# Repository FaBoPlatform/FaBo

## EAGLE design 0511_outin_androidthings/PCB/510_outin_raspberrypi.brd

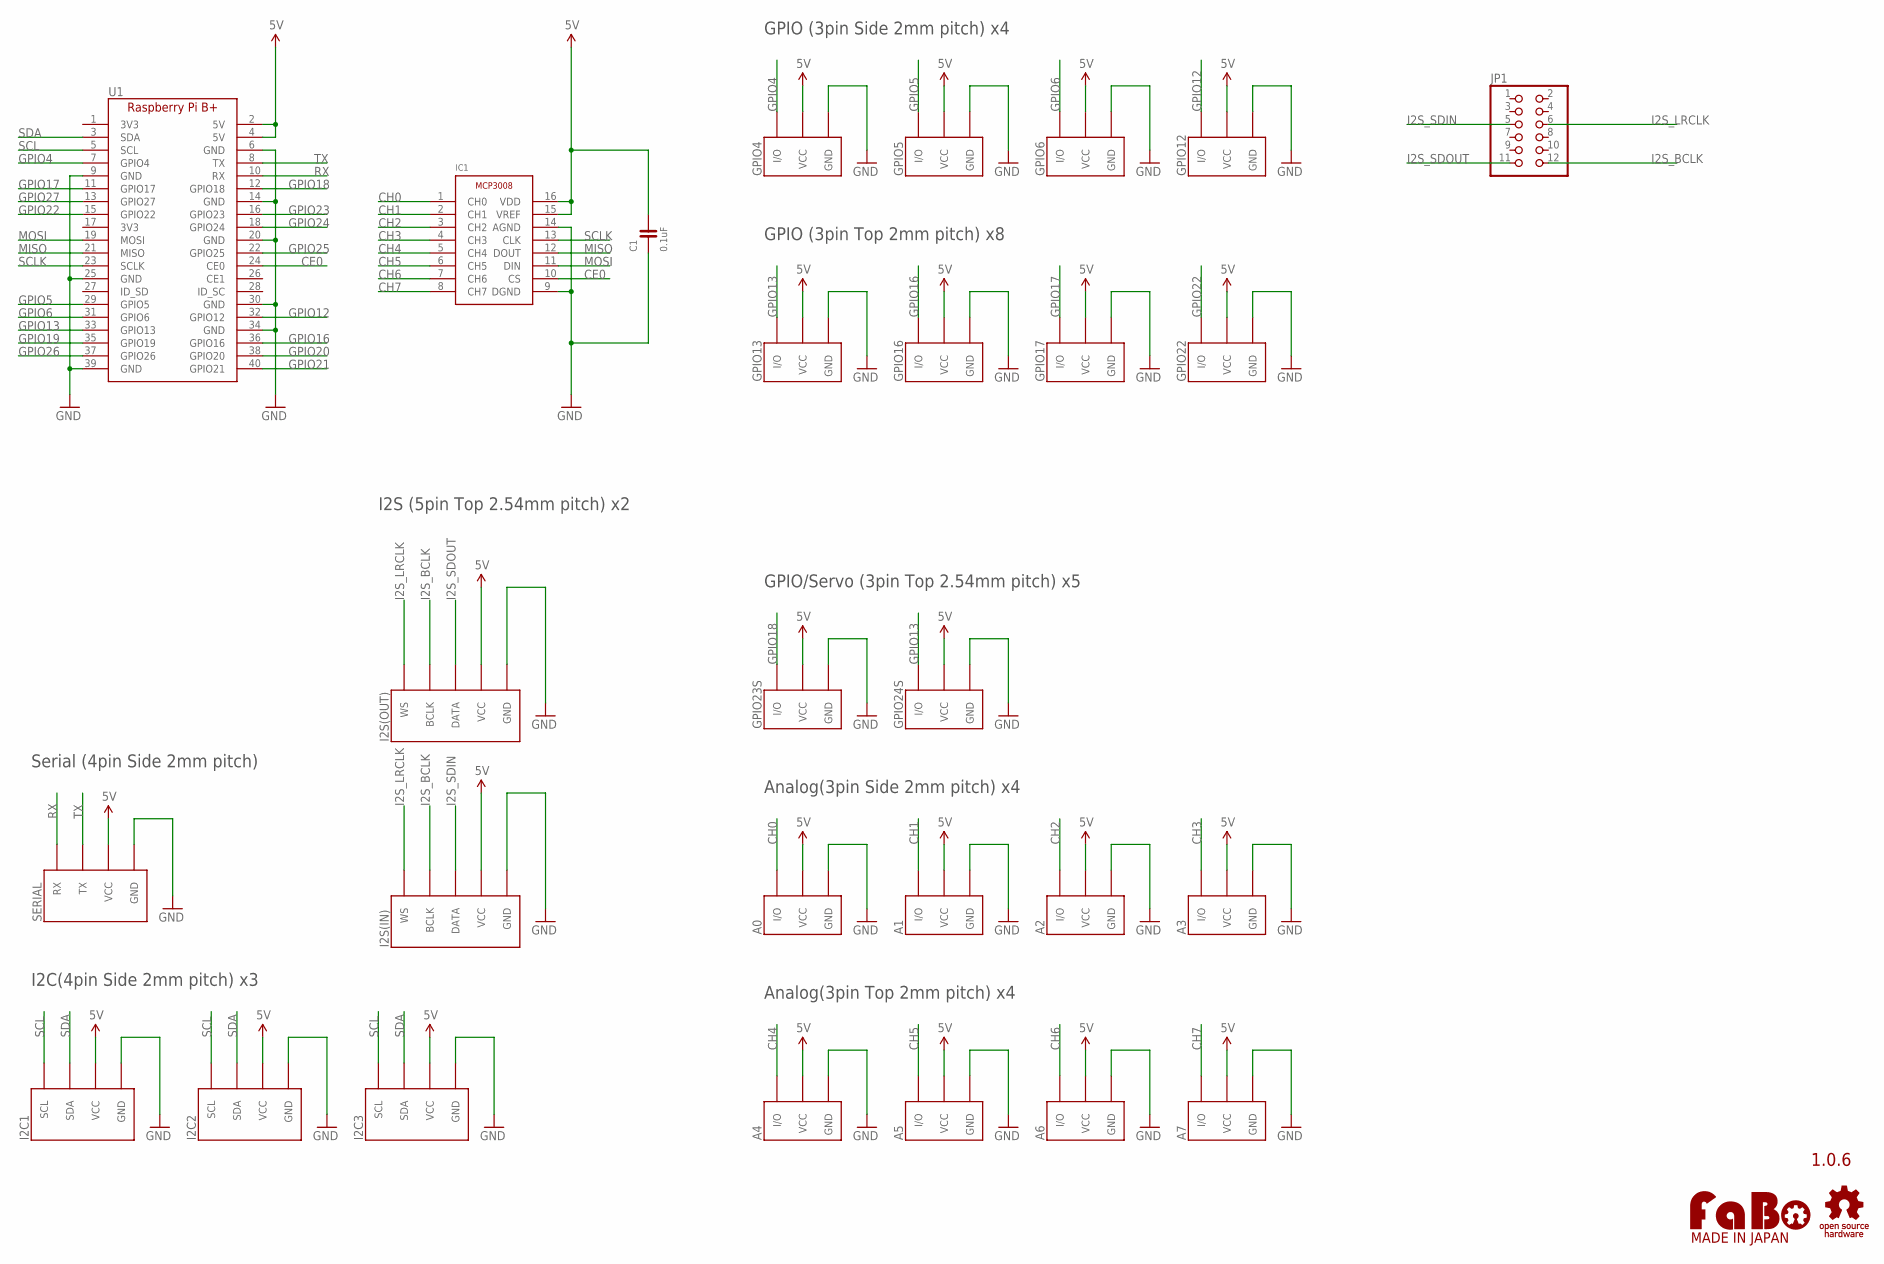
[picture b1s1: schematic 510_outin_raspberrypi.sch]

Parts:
A0, A1, A2, A3: FABO_BRICK_3PIN-S03B-PASK-2; FABO_BRICK_3PIN_S03B-PASK-2
A4, A5, A6, A7: FABO_BRICK_3PIN-B03B-PASK-1; FABO_BRICK_3PIN_B03B-PASK-1
C1: 0.1uF; 0603
GPIO4, GPIO5, GPIO6, GPIO12: FABO_BRICK_3PIN-S03B-PASK-2; FABO_BRICK_3PIN_S03B-PASK-2
GPIO13, GPIO16, GPIO17, GPIO22: FABO_BRICK_3PIN-B03B-PASK-1; FABO_BRICK_3PIN_B03B-PASK-1
GPIO23S, GPIO24S: FABO_BRICK_3PIN-HEADER; FABO_BRICK_3PIN_HEADER
I2C1, I2C2, I2C3: FABO_BRICK_I2C-S04B-PASK-2; FABO_BRICK_I2C_S04B-PASK-2
I2S(IN), I2S(OUT): FABO_BRICK_I2SLONG; FABO_BRICK_I2S_S05B-PASK-2_LONG
IC1: MICROCHIP-MCP3008
JP1: PINHD-2X6; 2X06
SERIAL: FABO_BRICK_SERIAL-S04B-PASK-2; FABO_BRICK_SERIAL_S04B-PASK-2
U1: RASPBERRY_PI_B+
U$4: LOGO_OSHW-T_M_BOTTOM; LOGO_OSHW_T_MS_BOTTOM
U$14: LOGO_FABO-M; LOGO_FABO_MS

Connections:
5V: A0.VCC, A1.VCC, A2.VCC, A3.VCC, A4.VCC, A5.VCC, A6.VCC, A7.VCC, C1.2, GPIO4.VCC, GPIO5.VCC, GPIO6.VCC, GPIO12.VCC, GPIO13.VCC, GPIO16.VCC, GPIO17.VCC, GPIO22.VCC, GPIO23S.VCC, GPIO24S.VCC, I2C1.VCC, I2C2.VCC, I2C3.VCC, I2S(IN).VCC, I2S(OUT).VCC, IC1.15 (VREF), IC1.16 (VDD), SERIAL.VCC, U1.2 (5V), U1.4 (5V)
CE0: IC1.10 (CS), U1.24 (CE0)
CH0: A0.I/O, IC1.1 (CH0)
CH1: A1.I/O, IC1.2 (CH1)
CH2: A2.I/O, IC1.3 (CH2)
CH3: A3.I/O, IC1.4 (CH3)
CH4: A4.I/O, IC1.5 (CH4)
CH5: A5.I/O, IC1.6 (CH5)
CH6: A6.I/O, IC1.7 (CH6)
CH7: A7.I/O, IC1.8 (CH7)
GND: A0.GND, A1.GND, A2.GND, A3.GND, A4.GND, A5.GND, A6.GND, A7.GND, C1.1, GPIO4.GND, GPIO5.GND, GPIO6.GND, GPIO12.GND, GPIO13.GND, GPIO16.GND, GPIO17.GND, GPIO22.GND, GPIO23S.GND, GPIO24S.GND, I2C1.GND, I2C2.GND, I2C3.GND, I2S(IN).GND, I2S(OUT).GND, IC1.9 (DGND), IC1.14 (AGND), SERIAL.GND, U1.6 (GND), U1.9 (GND), U1.14 (GND), U1.20 (GND), U1.25 (GND), U1.30 (GND), U1.34 (GND), U1.39 (GND)
GPIO4: GPIO4.I/O, U1.7 (GPIO4)
GPIO5: GPIO5.I/O, U1.29 (GPIO5)
GPIO6: GPIO6.I/O, U1.31 (GPIO6)
GPIO12: GPIO12.I/O, U1.32 (GPIO12)
GPIO13: GPIO13.I/O, GPIO24S.I/O, U1.33 (GPIO13)
GPIO16: GPIO16.I/O, U1.36 (GPIO16)
GPIO17: GPIO17.I/O, U1.11 (GPIO17)
GPIO18: GPIO23S.I/O, U1.12 (GPIO18)
GPIO19: U1.35 (GPIO19)
GPIO20: U1.38 (GPIO20)
GPIO21: U1.40 (GPIO21)
GPIO22: GPIO22.I/O, U1.15 (GPIO22)
GPIO23: U1.16 (GPIO23)
GPIO24: U1.18 (GPIO24)
GPIO25: U1.22 (GPIO25)
GPIO26: U1.37 (GPIO26)
GPIO27: U1.13 (GPIO27)
I2S_BCLK: I2S(IN).BCLK, I2S(OUT).BCLK, JP1.12
I2S_LRCLK: I2S(IN).WS, I2S(OUT).WS, JP1.6
I2S_SDIN: I2S(IN).DATA, JP1.5
I2S_SDOUT: I2S(OUT).DATA, JP1.11
MISO: IC1.12 (DOUT), U1.21 (MISO)
MOSI: IC1.11 (DIN), U1.19 (MOSI)
RX: SERIAL.RX, U1.10 (RX)
SCL: I2C1.SCL, I2C2.SCL, I2C3.SCL, U1.5 (SCL)
SCLK: IC1.13 (CLK), U1.23 (SCLK)
SDA: I2C1.SDA, I2C2.SDA, I2C3.SDA, U1.3 (SDA)
TX: SERIAL.TX, U1.8 (TX)

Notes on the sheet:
1.0.6
GPIO (3pin Side 2mm pitch) x4
I2C(4pin Side 2mm pitch) x3
Analog(3pin Side 2mm pitch) x4
Serial (4pin Side 2mm pitch)
GPIO (3pin Top 2mm pitch) x8
GPIO/Servo (3pin Top 2.54mm pitch) x5
Analog(3pin Top 2mm pitch) x4
I2S (5pin Top 2.54mm pitch) x2

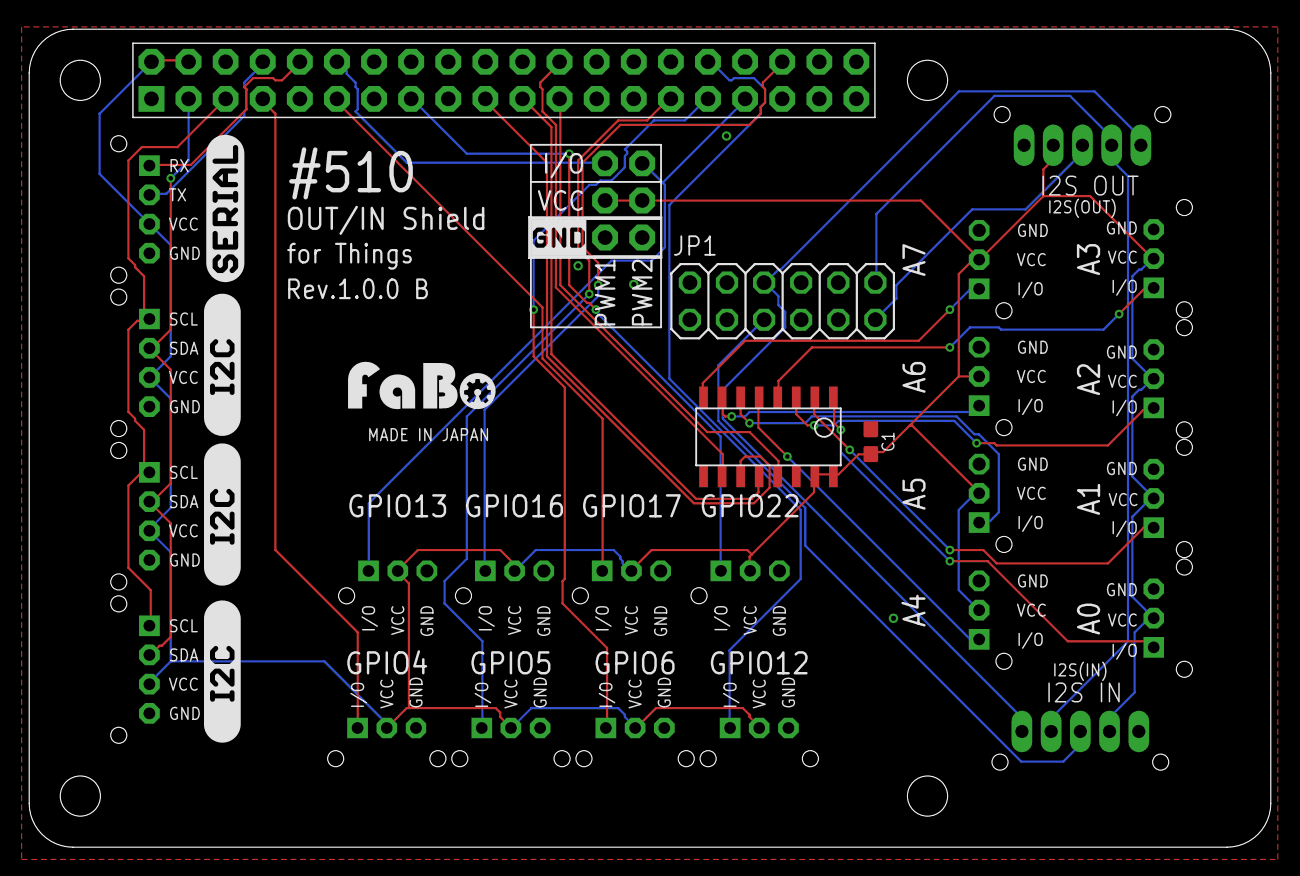
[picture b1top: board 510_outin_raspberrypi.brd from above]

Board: 2 copper layers, 85.0 x 56.0 mm, 35 parts (0 on the bottom side), 31 nets.

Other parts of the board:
U$2, U$5, U$6: LOGO_SILK_I2C
U$3: LOGO_SILK_SERIAL2
U$7: LOGO_SILK_GND

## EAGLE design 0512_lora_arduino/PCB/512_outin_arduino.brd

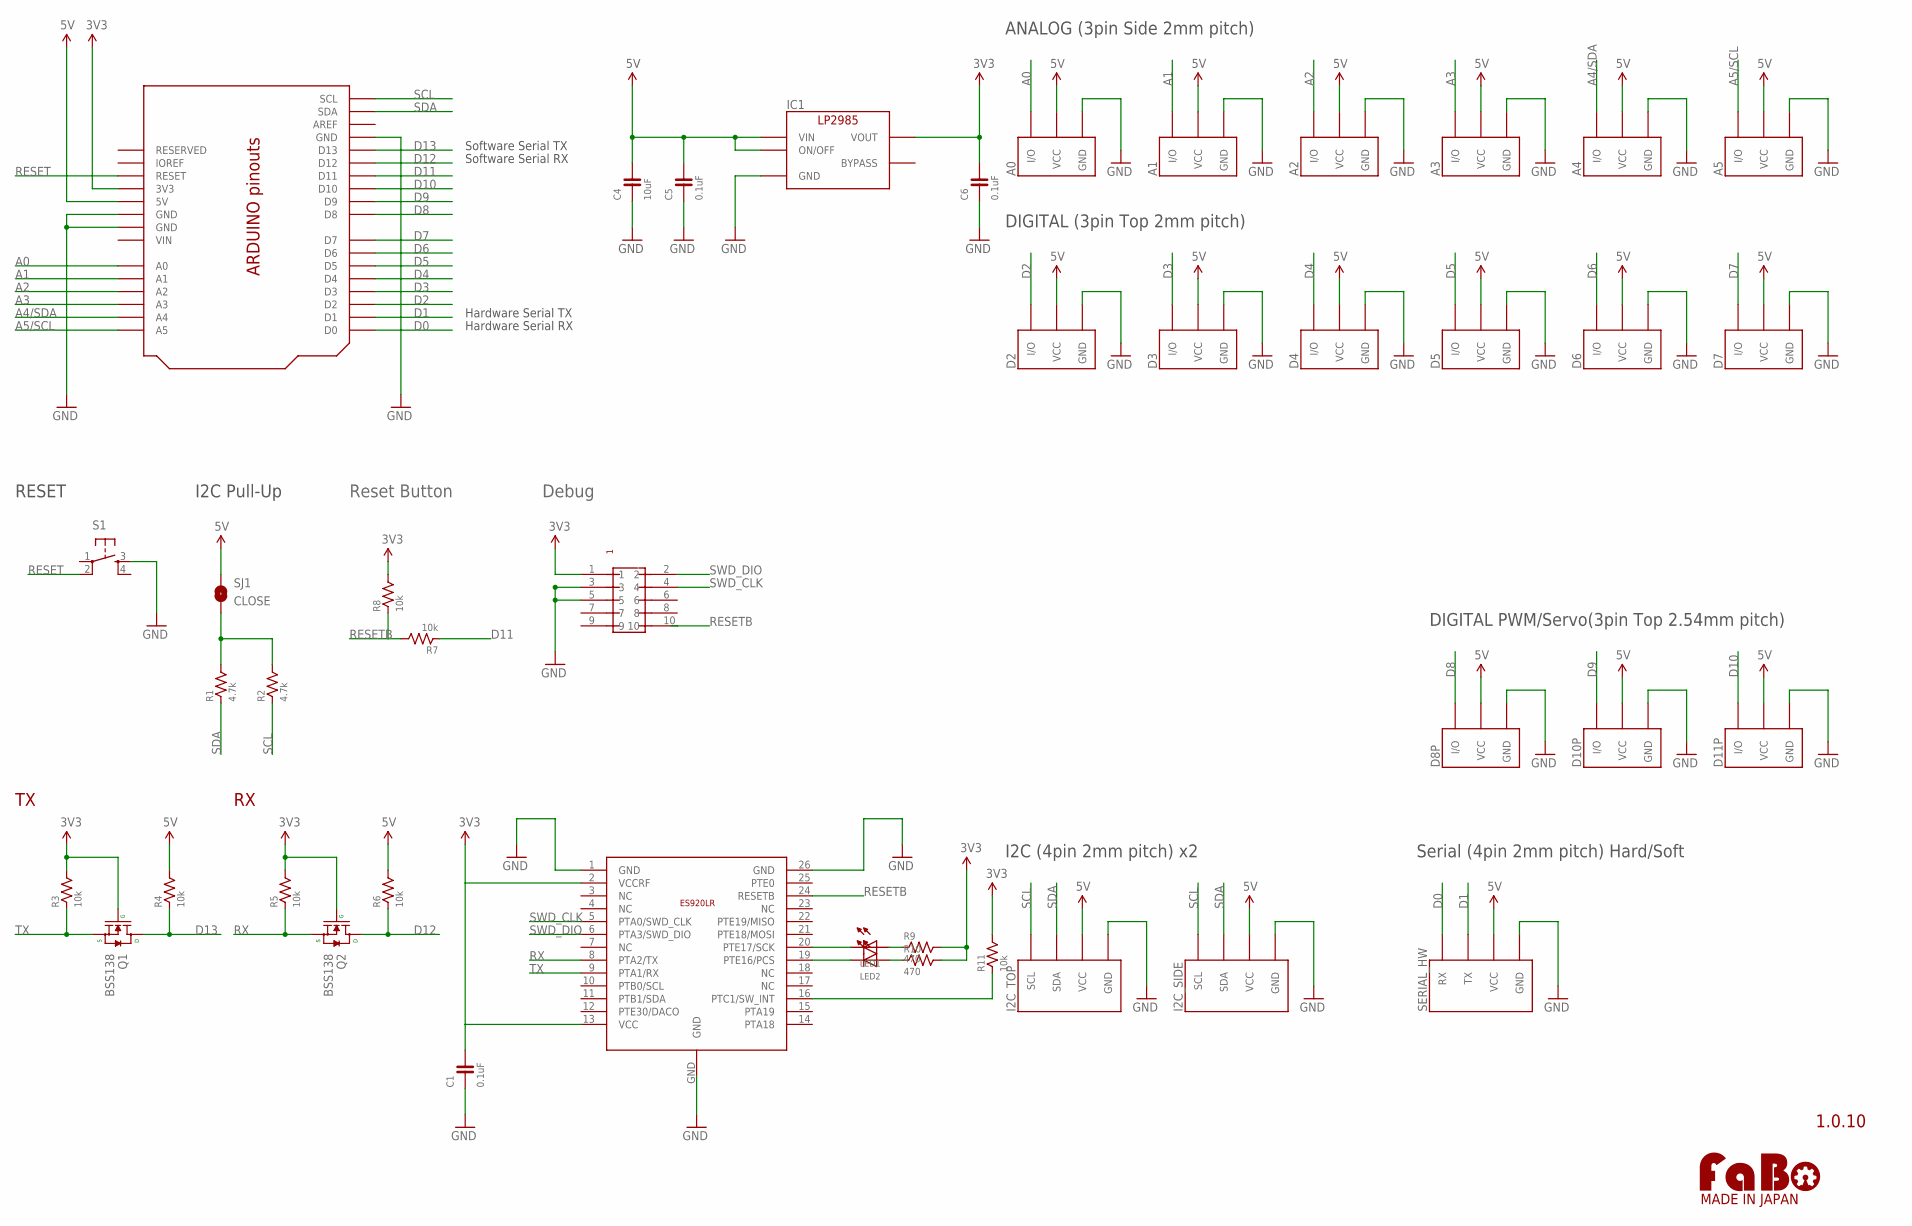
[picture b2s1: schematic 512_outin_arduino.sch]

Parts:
A0, A1, A2, A3, A4, A5: FABO_BRICK_3PIN-S03B-PASK-2_LONG; FABO_BRICK_3PIN_S03B-PASK-2_LONG
C1, C5, C6: 0.1uF; 0603-NARROW
C4: 10uF; 0603-NARROW
D2, D3, D4, D5, D6, D7: FABO_BRICK_3PIN-B03B-PASK-1; FABO_BRICK_3PIN_B03B-PASK-1
D8P, D10P, D11P: FABO_BRICK_3PIN-HEADER; FABO_BRICK_3PIN_HEADER
I2C_SIDE: FABO_BRICK_I2C-S04B-PASK-2_LONG; FABO_BRICK_I2C_S04B-PASK-2_LONG
I2C_TOP: FABO_BRICK_I2C-B04B-PASK-1; FABO_BRICK_I2C_B04B-PASK-1
IC1: LP2985-33DBV; SOT-23-5
LED1, LED2: LED-0603; 0603
Q1, Q2: BSS138; SOT23-3
R1, R2: 4.7k; 0603
R3, R4, R5, R6, R7, R8, R11: 10k; 0603-NARROW
R9, R10: 470; 0603-NARROW
S1: TACT-SWITCH-6MM; DTS_6_V
SERIAL_HW: FABO_BRICK_SERIAL-B04B-PASK-1; FABO_BRICK_SERIAL_B04B-PASK-1
SJ1: CLOSE; SMD-JUMPER-2-CLOSE
U1: ARDUINO_UNO_R3_SHIELD-OUTIN; ARDUINO_SHIELD_OUTIN
U$10: LOGO_FABO-M; LOGO_FABO_MS
U$15: PIN-HEADER-SMT(1.27MM)2X5
U$16: ES920LR

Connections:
3V3: C1.2, C6.2, IC1.5 (VOUT), Q1.1 (G), Q2.1 (G), R3.2, R5.2, R8.2, R9.2, R10.2, R11.2, U1.3V3, U$15.1, U$16.2 (VCCRF), U$16.13 (VCC)
5V: A0.VCC, A1.VCC, A2.VCC, A3.VCC, A4.VCC, A5.VCC, C4.2, C5.2, D2.VCC, D3.VCC, D4.VCC, D5.VCC, D6.VCC, D7.VCC, D8P.VCC, D10P.VCC, D11P.VCC, I2C_SIDE.VCC, I2C_TOP.VCC, IC1.1 (VIN), IC1.3 (ON/OFF), R4.2, R6.2, SERIAL_HW.VCC, SJ1.1, U1.5V
A0: A0.I/O, U1.A0
A1: A1.I/O, U1.A1
A2: A2.I/O, U1.A2
A3: A3.I/O, U1.A3
A4/SDA: A4.I/O, U1.A4
A5/SCL: A5.I/O, U1.A5
D0: SERIAL_HW.RX, U1.D0
D1: SERIAL_HW.TX, U1.D1
D2: D2.I/O, U1.D2
D3: D3.I/O, U1.D3
D4: D4.I/O, U1.D4
D5: D5.I/O, U1.D5
D6: D6.I/O, U1.D6
D7: D7.I/O, U1.D7
D8: D8P.I/O, U1.D8
D9: D10P.I/O, U1.D9
D10: D11P.I/O, U1.D10
D11: R7.1, U1.D11
D12: Q2.3 (D), R6.1, U1.D12
D13: Q1.3 (D), R4.1, U1.D13
GND: A0.GND, A1.GND, A2.GND, A3.GND, A4.GND, A5.GND, C1.1, C4.1, C5.1, C6.1, D2.GND, D3.GND, D4.GND, D5.GND, D6.GND, D7.GND, D8P.GND, D10P.GND, D11P.GND, I2C_SIDE.GND, I2C_TOP.GND, IC1.2 (GND), S1.3, SERIAL_HW.GND, U1.GND1 (GND), U1.GND2 (GND), U1.GND3 (GND), U$15.3, U$15.5, U$16.1 (GND), U$16.26 (GND), U$16.GND
unnamed: R1.2, R2.2, SJ1.2
unnamed: LED2.CATHODE, U$16.19 (PTE16/PCS)
unnamed: LED1.CATHODE, U$16.20 (PTE17/SCK)
unnamed: LED1.ANODE, R9.1
unnamed: LED2.ANODE, R10.1
unnamed: R11.1, U$16.16 (PTC1/SW_INT)
RESET: S1.2, U1.RESET
RESETB: R7.2, R8.1, U$15.10, U$16.24 (RESETB)
RX: Q2.2 (S), R5.1, U$16.8 (PTA2/TX)
SCL: I2C_SIDE.SCL, I2C_TOP.SCL, R2.1, U1.SCL
SDA: I2C_SIDE.SDA, I2C_TOP.SDA, R1.1, U1.SDA
SWD_CLK: U$15.4, U$16.5 (PTA0/SWD_CLK)
SWD_DIO: U$15.2, U$16.6 (PTA3/SWD_DIO)
TX: Q1.2 (S), R3.1, U$16.9 (PTA1/RX)
VIN: U1.VIN

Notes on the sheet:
1.0.10
DIGITAL (3pin Top 2mm pitch)
ANALOG (3pin Side 2mm pitch)
DIGITAL PWM/Servo(3pin Top 2.54mm pitch)
I2C (4pin 2mm pitch) x2
Software Serial RX
Software Serial TX
Serial (4pin 2mm pitch) Hard/Soft
Hardware Serial TX
Hardware Serial RX
I2C Pull-Up
RESET
Reset Button
Debug

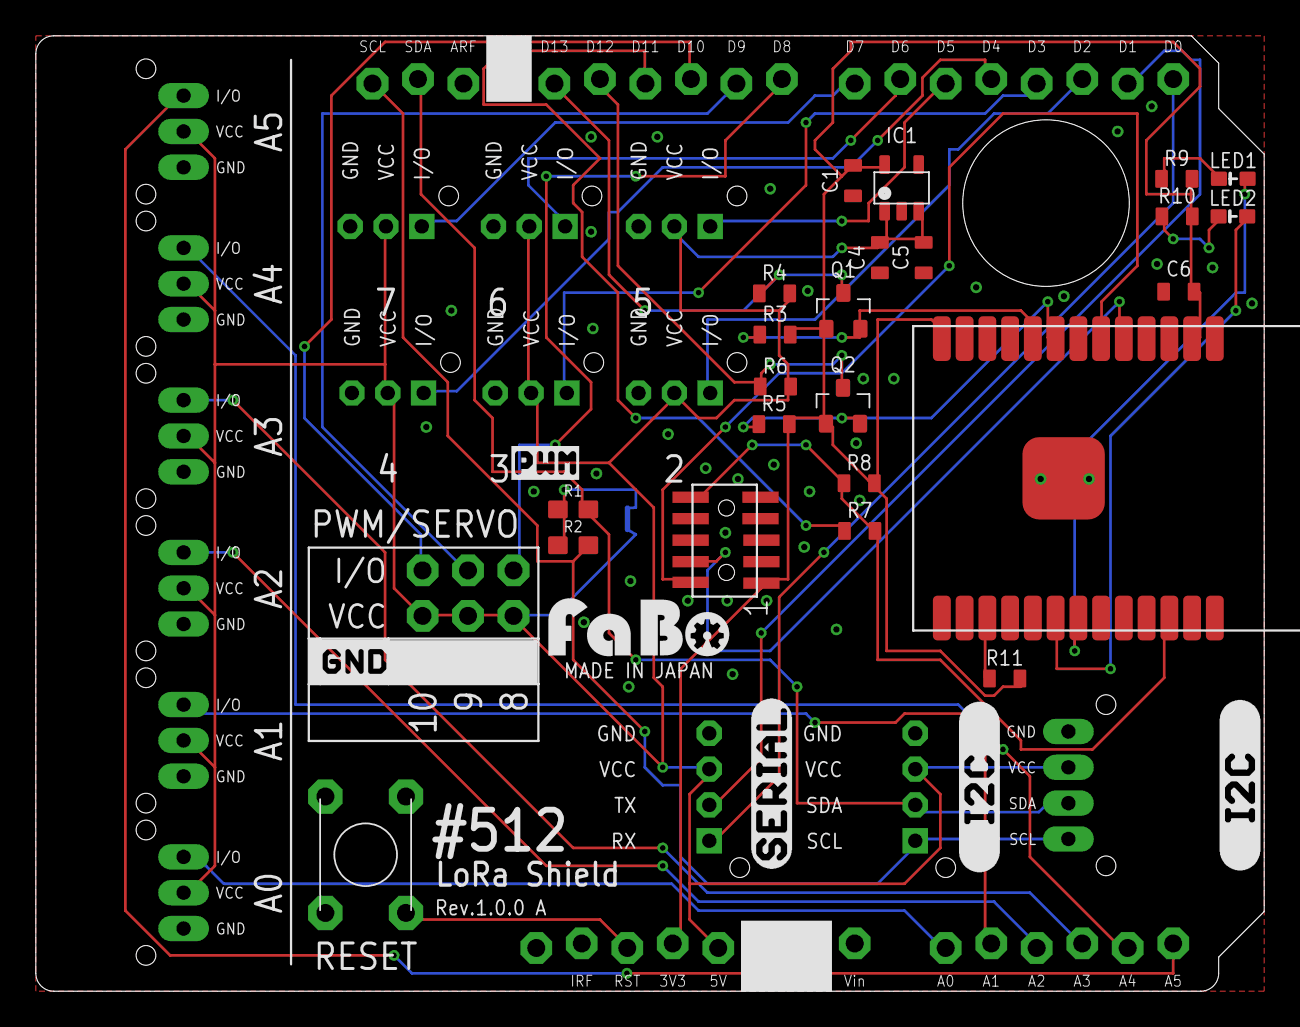
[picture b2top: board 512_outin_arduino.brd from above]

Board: 2 copper layers, 68.6 x 53.3 mm, 49 parts (1 on the bottom side), 37 nets.

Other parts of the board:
U$2: LOGO_SILK_SERIAL2
U$5: LOGO_SILK_PWM
U$11, U$12: LOGO_SILK_I2C
U$19: LOGO_SILK_GND

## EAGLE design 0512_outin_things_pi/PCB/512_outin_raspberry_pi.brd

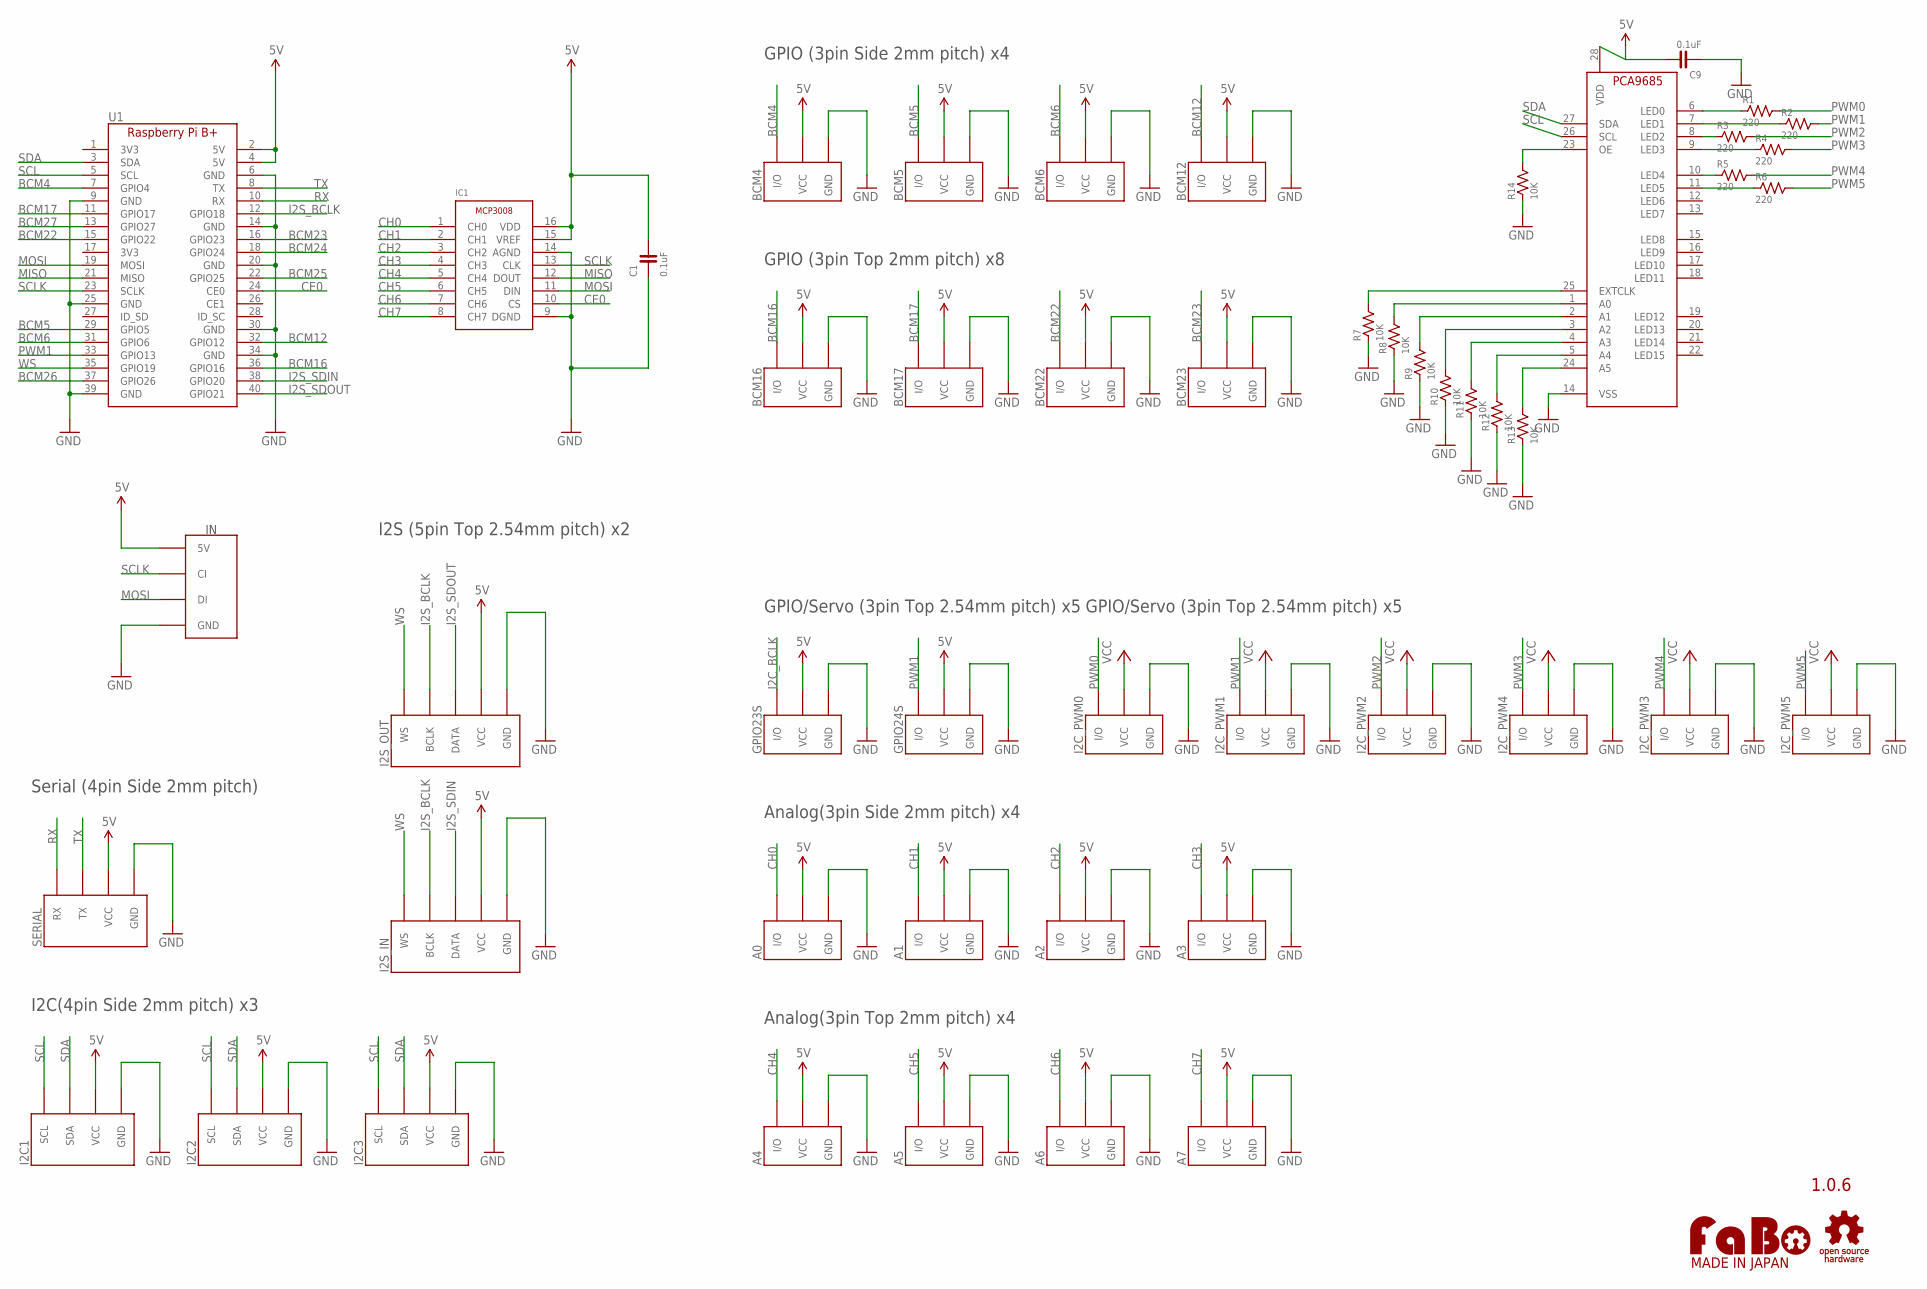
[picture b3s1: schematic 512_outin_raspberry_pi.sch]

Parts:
A0, A1, A2, A3: FABO_BRICK_3PIN-S03B-PASK-2; FABO_BRICK_3PIN_S03B-PASK-2
A4, A5, A6, A7: FABO_BRICK_3PIN-B03B-PASK-1; FABO_BRICK_3PIN_B03B-PASK-1
BCM4, BCM5, BCM6, BCM12: FABO_BRICK_3PIN-S03B-PASK-2; FABO_BRICK_3PIN_S03B-PASK-2
BCM16, BCM17, BCM22, BCM23: FABO_BRICK_3PIN-B03B-PASK-1; FABO_BRICK_3PIN_B03B-PASK-1
C1, C9: 0.1uF; 0603
GPIO23S, GPIO24S: FABO_BRICK_3PIN-HEADER; FABO_BRICK_3PIN_HEADER
I2C1, I2C2, I2C3: FABO_BRICK_I2C-S04B-PASK-2; FABO_BRICK_I2C_S04B-PASK-2
I2C_PWM0, I2C_PWM1, I2C_PWM2, I2C_PWM3, I2C_PWM4, I2C_PWM5: FABO_BRICK_3PIN-HEADER; FABO_BRICK_3PIN_HEADER
I2S_IN, I2S_OUT: FABO_BRICK_I2STOP; FABO_BRICK_I2S_B05B-PARK-1
IC1: MICROCHIP-MCP3008
LED: FABO_BRICK_SPI_LED
R1, R2, R3, R4, R5, R6: 220; 0603
R7, R8, R9, R10, R11, R12, R13, R14: 10K; 0603
SERIAL: FABO_BRICK_SERIAL-S04B-PASK-2; FABO_BRICK_SERIAL_S04B-PASK-2
U1: RASPBERRY_PI_B+NORMAL; RASPBERRY_PI_B+
U$4: LOGO_OSHW-T_M_BOTTOM; LOGO_OSHW_T_MS_BOTTOM
U$9: PCA9685
U$14: LOGO_FABO-M; LOGO_FABO_MS

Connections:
5V: A0.VCC, A1.VCC, A2.VCC, A3.VCC, A4.VCC, A5.VCC, A6.VCC, A7.VCC, BCM4.VCC, BCM5.VCC, BCM6.VCC, BCM12.VCC, BCM16.VCC, BCM17.VCC, BCM22.VCC, BCM23.VCC, C1.2, C9.2, GPIO23S.VCC, GPIO24S.VCC, I2C1.VCC, I2C2.VCC, I2C3.VCC, I2S_IN.VCC, I2S_OUT.VCC, IC1.15 (VREF), IC1.16 (VDD), LED.5V, SERIAL.VCC, U1.2 (5V), U1.4 (5V), U$9.28 (VDD)
BCM4: BCM4.I/O, U1.7 (GPIO4)
BCM5: BCM5.I/O, U1.29 (GPIO5)
BCM6: BCM6.I/O, U1.31 (GPIO6)
BCM12: BCM12.I/O, U1.32 (GPIO12)
BCM16: BCM16.I/O, U1.36 (GPIO16)
BCM17: BCM17.I/O, U1.11 (GPIO17)
BCM22: BCM22.I/O, U1.15 (GPIO22)
BCM23: BCM23.I/O, U1.16 (GPIO23)
BCM24: U1.18 (GPIO24)
BCM25: U1.22 (GPIO25)
BCM26: U1.37 (GPIO26)
BCM27: U1.13 (GPIO27)
CE0: IC1.10 (CS), U1.24 (CE0)
CH0: A0.I/O, IC1.1 (CH0)
CH1: A1.I/O, IC1.2 (CH1)
CH2: A2.I/O, IC1.3 (CH2)
CH3: A3.I/O, IC1.4 (CH3)
CH4: A4.I/O, IC1.5 (CH4)
CH5: A5.I/O, IC1.6 (CH5)
CH6: A6.I/O, IC1.7 (CH6)
CH7: A7.I/O, IC1.8 (CH7)
GND: A0.GND, A1.GND, A2.GND, A3.GND, A4.GND, A5.GND, A6.GND, A7.GND, BCM4.GND, BCM5.GND, BCM6.GND, BCM12.GND, BCM16.GND, BCM17.GND, BCM22.GND, BCM23.GND, C1.1, C9.1, GPIO23S.GND, GPIO24S.GND, I2C1.GND, I2C2.GND, I2C3.GND, I2C_PWM0.GND, I2C_PWM1.GND, I2C_PWM2.GND, I2C_PWM3.GND, I2C_PWM4.GND, I2C_PWM5.GND, I2S_IN.GND, I2S_OUT.GND, IC1.9 (DGND), IC1.14 (AGND), LED.GND, R7.1, R8.1, R9.1, R10.1, R11.1, R12.1, R13.1, R14.1, SERIAL.GND, U1.6 (GND), U1.9 (GND), U1.14 (GND), U1.20 (GND), U1.25 (GND), U1.30 (GND), U1.34 (GND), U1.39 (GND), U$9.14 (VSS)
I2C_BCLK: GPIO23S.I/O
I2S_BCLK: I2S_IN.BCLK, I2S_OUT.BCLK, U1.12 (GPIO18)
I2S_SDIN: I2S_IN.DATA, U1.38 (GPIO20)
I2S_SDOUT: I2S_OUT.DATA, U1.40 (GPIO21)
LED0: R1.1, U$9.6 (LED0)
LED1: R2.1, U$9.7 (LED1)
LED2: R3.1, U$9.8 (LED2)
LED3: R4.1, U$9.9 (LED3)
LED4: R5.1, U$9.10 (LED4)
LED5: R6.1, U$9.11 (LED5)
MISO: IC1.12 (DOUT), U1.21 (MISO)
MOSI: IC1.11 (DIN), LED.DI, U1.19 (MOSI)
unnamed: R14.2, U$9.23 (OE)
unnamed: R7.2, U$9.25 (EXTCLK)
unnamed: R8.2, U$9.1 (A0)
unnamed: R9.2, U$9.2 (A1)
unnamed: R10.2, U$9.3 (A2)
unnamed: R11.2, U$9.4 (A3)
unnamed: R12.2, U$9.5 (A4)
unnamed: R13.2, U$9.24 (A5)
PWM0: I2C_PWM0.I/O, R1.2
PWM1: GPIO24S.I/O, I2C_PWM1.I/O, R2.2, U1.33 (GPIO13)
PWM2: I2C_PWM2.I/O, R3.2
PWM3: I2C_PWM4.I/O, R4.2
PWM4: I2C_PWM3.I/O, R5.2
PWM5: I2C_PWM5.I/O, R6.2
RX: SERIAL.RX, U1.10 (RX)
SCL: I2C1.SCL, I2C2.SCL, I2C3.SCL, U1.5 (SCL), U$9.26 (SCL)
SCLK: IC1.13 (CLK), LED.CI, U1.23 (SCLK)
SDA: I2C1.SDA, I2C2.SDA, I2C3.SDA, U1.3 (SDA), U$9.27 (SDA)
TX: SERIAL.TX, U1.8 (TX)
VCC: I2C_PWM0.VCC, I2C_PWM1.VCC, I2C_PWM2.VCC, I2C_PWM3.VCC, I2C_PWM4.VCC, I2C_PWM5.VCC
WS: I2S_IN.WS, I2S_OUT.WS, U1.35 (GPIO19)

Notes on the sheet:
1.0.6
GPIO (3pin Side 2mm pitch) x4
I2C(4pin Side 2mm pitch) x3
Analog(3pin Side 2mm pitch) x4
Serial (4pin Side 2mm pitch)
GPIO (3pin Top 2mm pitch) x8
GPIO/Servo (3pin Top 2.54mm pitch) x5
Analog(3pin Top 2mm pitch) x4
I2S (5pin Top 2.54mm pitch) x2

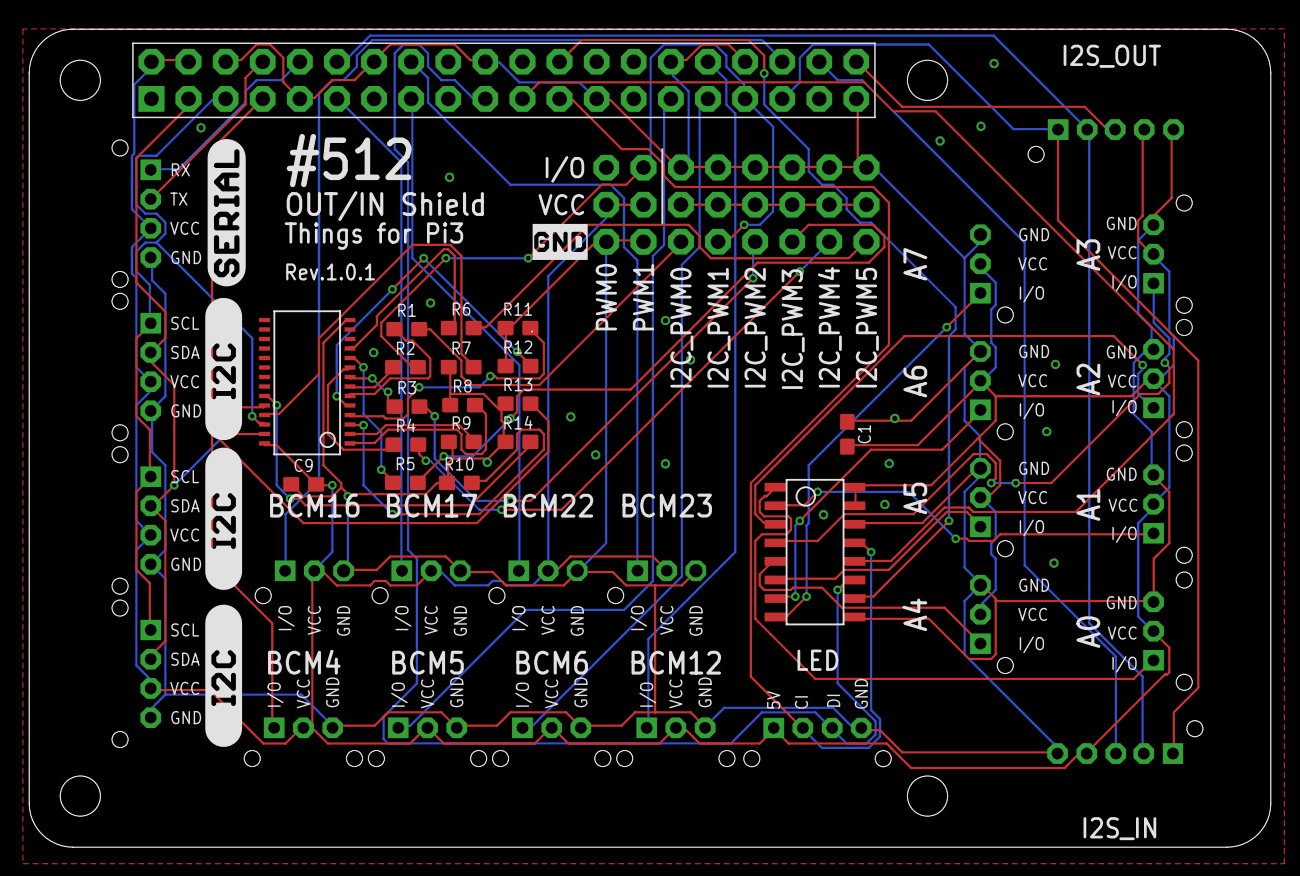
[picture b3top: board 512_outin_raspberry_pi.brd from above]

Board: 2 copper layers, 85.0 x 56.0 mm, 57 parts (0 on the bottom side), 51 nets.

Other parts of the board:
LOGO1: LOGO_FABO_M_BOTTOM
U$2, U$5, U$6: LOGO_SILK_I2C
U$3: LOGO_SILK_SERIAL2
U$7: LOGO_SILK_GND

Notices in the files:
parts and their libraries:
FaBo-etc: Released under the Creative Commons Attribution-ShareAlike 4.0 License
https://creativecommons.org/licenses/by-sa/4.0
FaBo-etc: Released under the Creative Commons
